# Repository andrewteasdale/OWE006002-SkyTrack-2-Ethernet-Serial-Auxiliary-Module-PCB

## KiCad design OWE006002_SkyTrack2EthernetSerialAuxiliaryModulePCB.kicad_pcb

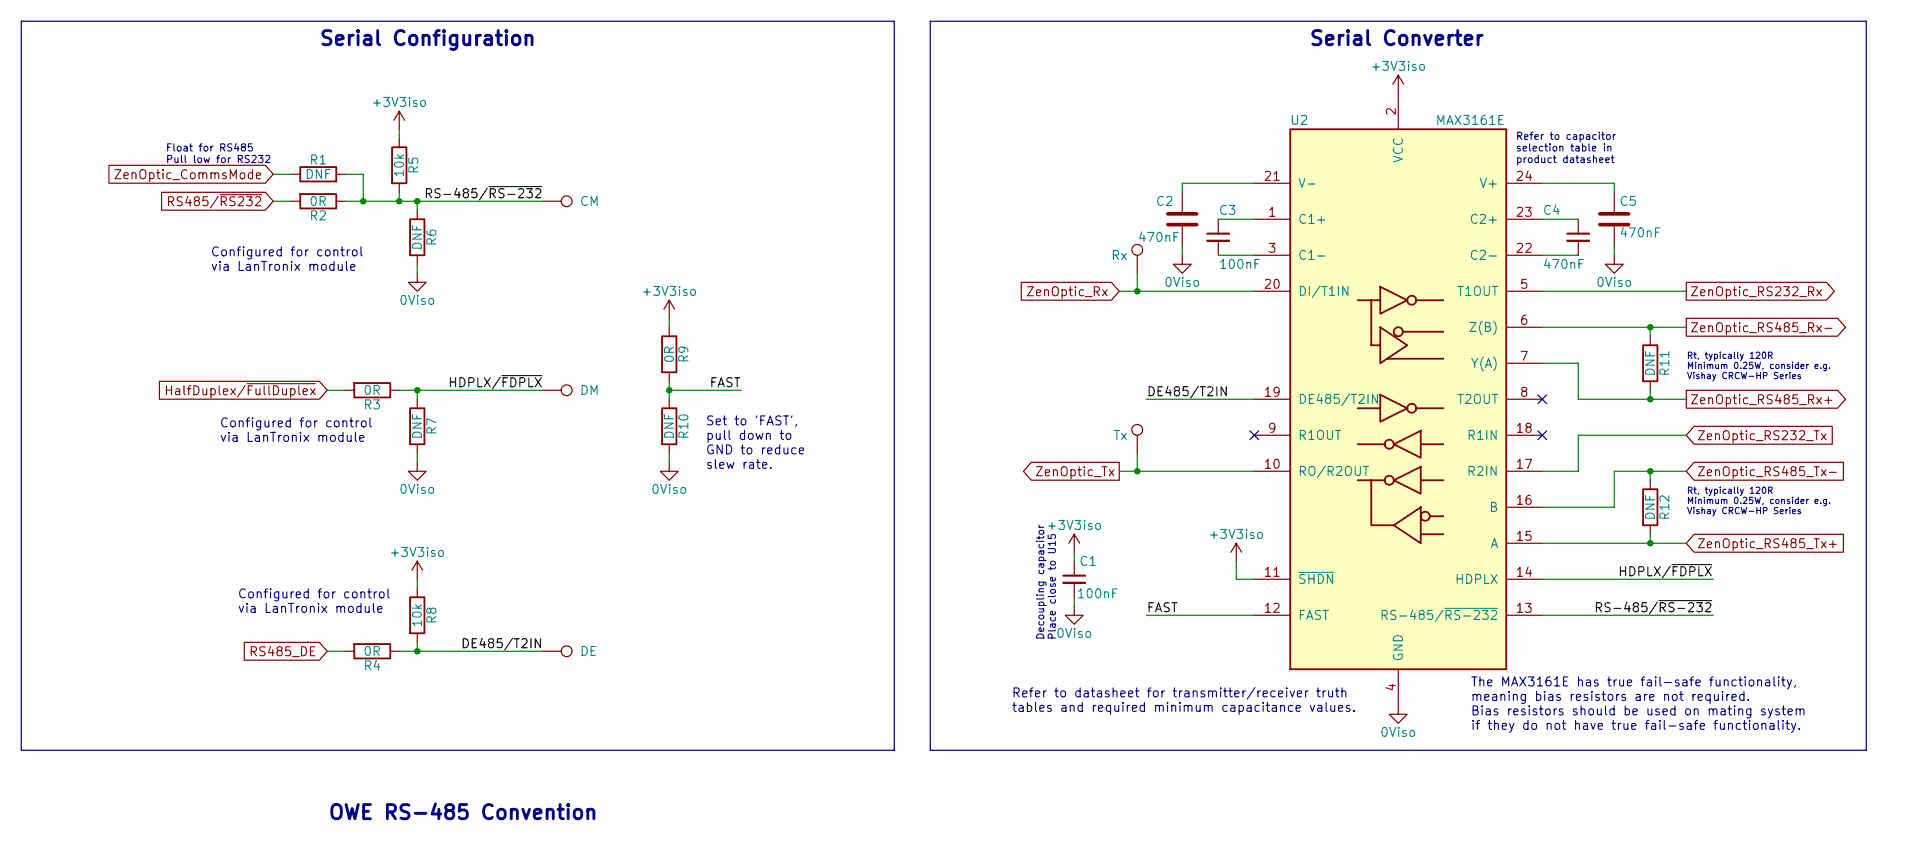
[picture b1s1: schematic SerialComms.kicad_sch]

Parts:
C1, C3: 100nF; C_0603_1608Metric
C2, C4, C5: 470nF; C_0603_1608Metric
R1, R6, R7, R10: DNF; R_0603_1608Metric
R2, R3, R4, R9: 0R; R_0603_1608Metric
R5, R8: 10k; R_0603_1608Metric
R11, R12: DNF; R_1206_3216Metric
TP1: Rx; TestPoint_THTPad_D1.0mm_Drill0.5mm
TP2: Tx; TestPoint_THTPad_D1.0mm_Drill0.5mm
TP3: CM; TestPoint_THTPad_D1.0mm_Drill0.5mm
TP4: DM; TestPoint_THTPad_D1.0mm_Drill0.5mm
TP5: DE; TestPoint_THTPad_D1.0mm_Drill0.5mm
U2: MAX3161E; SSOP-24_5.3x8.2mm_P0.65mm

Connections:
0Viso: C1.2, C2.2, C5.2, R6.2, R7.2, R10.2, U2.4 (GND); also elsewhere on the board
+3V3iso: C1.1, R5.1, R8.1, R9.1, U2.2 (VCC), U2.11 (~SHDN); also elsewhere on the board
/Serial Comms/DE485/T2IN: R4.1, R8.2, TP5.1, U2.19 (DE485/T2IN)
/Serial Comms/FAST: R9.2, R10.1, U2.12 (FAST)
/Serial Comms/HDPLX/~FDPLX: R3.1, R7.1, TP4.1, U2.14 (HDPLX)
/Serial Comms/RS-485/~RS-232: R1.2, R2.1, R5.2, R6.1, TP3.1, U2.13 (RS-485/~RS-232)
HalfDuplex/~FullDuplex: R3.2; also elsewhere on the board
unnamed: C2.1, U2.21 (V-)
unnamed: C3.1, U2.1 (C1+)
unnamed: C3.2, U2.3 (C1-)
unnamed: C4.1, U2.23 (C2+)
unnamed: C4.2, U2.22 (C2-)
unnamed: C5.1, U2.24 (V+)
RS485_DE: R4.2; also elsewhere on the board
RS485/~RS232: R2.2; also elsewhere on the board
ZenOptic_CommsMode: R1.1; also elsewhere on the board
ZenOptic_RS232_Rx: U2.5 (T1OUT); also elsewhere on the board
ZenOptic_RS232_Tx: U2.17 (R2IN); also elsewhere on the board
ZenOptic_RS485_Rx+: R11.2, U2.7 (Y(A)); also elsewhere on the board
ZenOptic_RS485_Rx-: R11.1, U2.6 (Z(B)); also elsewhere on the board
ZenOptic_RS485_Tx+: R12.2, U2.15 (A); also elsewhere on the board
ZenOptic_RS485_Tx-: R12.1, U2.16 (B); also elsewhere on the board
ZenOptic_Rx: TP1.1, U2.20 (DI/T1IN); also elsewhere on the board
ZenOptic_Tx: TP2.1, U2.10 (RO/R2OUT); also elsewhere on the board

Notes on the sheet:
Decoupling capacitor Place close to U15
Refer to datasheet for transmitter/receiver truth tables and required minimum capacitance values.
Configured for control via LanTronix module
Set to 'FAST', pull down to GND to reduce slew rate.
Rt, typically 120R Minimum 0.25W, consider e.g. Vishay CRCW-HP Series
Serial Configuration
The MAX3161E has true fail-safe functionality, meaning bias resistors are not required. Bias resistors should be used on mating system if they do not have true fail-safe functionality.
OWE RS-485 Convention
Refer to capacitor selection table in product datasheet
Float for RS485 Pull low for RS232
Serial Converter

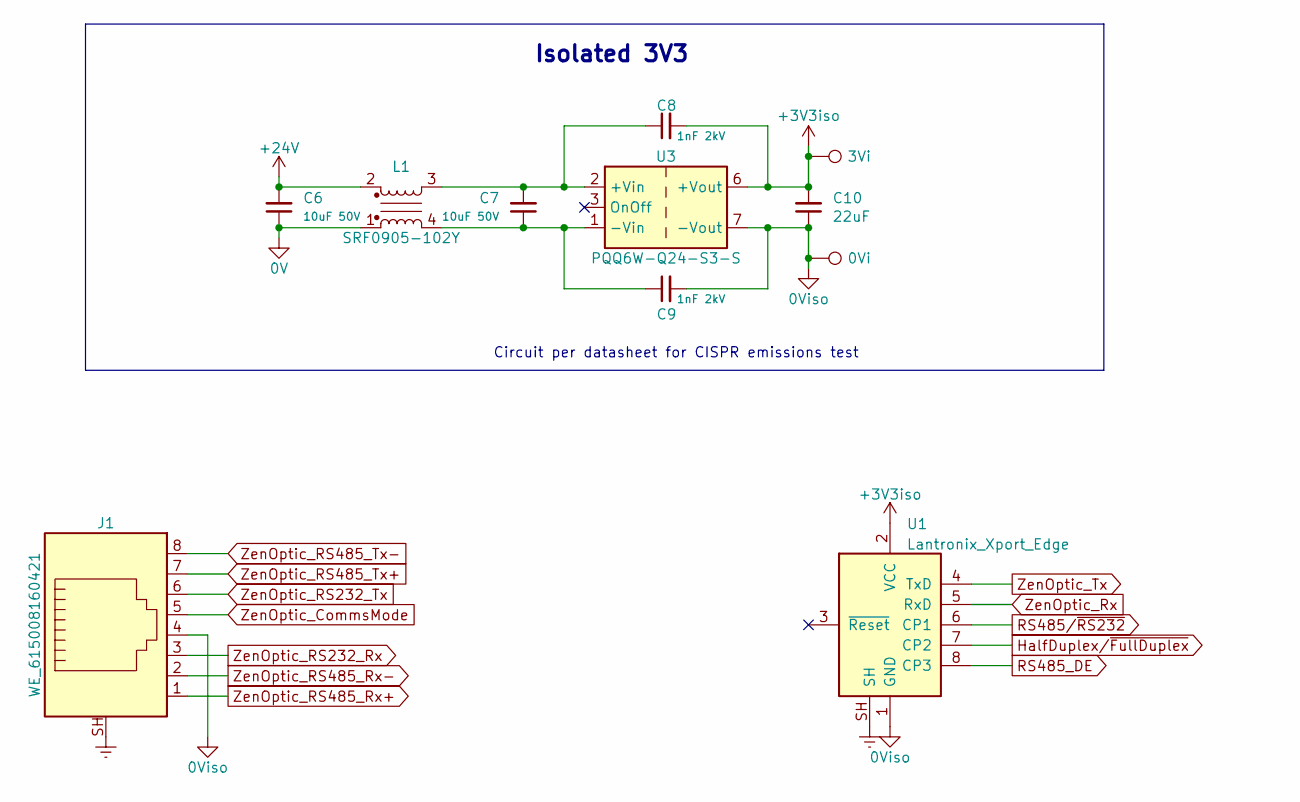
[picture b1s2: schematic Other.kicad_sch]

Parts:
C6, C7: 10uF 50V; C_1210_3225Metric
C8, C9: 1nF 2kV; C_1206_3216Metric
C10: 22uF; C_1210_3225Metric
J1: WE_615008160421; RJ45_WE_615008160421
L1: SRF0905-102Y; Filter_Bourns_SRF0905_6.0x9.2mm
TP6: 3Vi; TestPoint_THTPad_D1.0mm_Drill0.5mm
TP7: 0Vi; TestPoint_THTPad_D1.0mm_Drill0.5mm
U1: Lantronix_Xport_Edge; Lantronix_XPort_Edge
U3: PQQ6W-Q24-S3-S; Converter_DCDC_TRACO_TMR-xxxx_THT

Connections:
0V: C6.1, L1.1
0Viso: C9.2, C10.1, J1.4, TP7.1, U1.1 (GND), U3.7 (-Vout); also elsewhere on the board
+3V3iso: C8.2, C10.2, TP6.1, U1.2 (VCC), U3.6 (+Vout); also elsewhere on the board
+24V: C6.2, L1.2
Earth: J1.SH, U1.SH
HalfDuplex/~FullDuplex: U1.7 (CP2); also elsewhere on the board
unnamed: C7.1, C9.1, L1.4, U3.1 (-Vin)
unnamed: C7.2, C8.1, L1.3, U3.2 (+Vin)
RS485_DE: U1.8 (CP3); also elsewhere on the board
RS485/~RS232: U1.6 (CP1); also elsewhere on the board
ZenOptic_CommsMode: J1.5; also elsewhere on the board
ZenOptic_RS232_Rx: J1.3; also elsewhere on the board
ZenOptic_RS232_Tx: J1.6; also elsewhere on the board
ZenOptic_RS485_Rx+: J1.1; also elsewhere on the board
ZenOptic_RS485_Rx-: J1.2; also elsewhere on the board
ZenOptic_RS485_Tx+: J1.7; also elsewhere on the board
ZenOptic_RS485_Tx-: J1.8; also elsewhere on the board
ZenOptic_Rx: U1.5 (RxD); also elsewhere on the board
ZenOptic_Tx: U1.4 (TxD); also elsewhere on the board

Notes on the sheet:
Isolated 3V3
Circuit per datasheet for CISPR emissions test

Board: 2 copper layers, 34 parts (0 on the bottom side), 29 nets, no tracks yet.

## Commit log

2022-05-12 Initial commit of schematics
